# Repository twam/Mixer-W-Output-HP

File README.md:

Mixer-W-Output-HP
===

This repository is part of the USB audio mixer project described on https://www.twam.info/general/building-a-custom-usb-audio-mixer.

The 'W-Output HP' board is an W-Output compatible head phone amplifier, which can be used on
[W-DAC 4493](https://nihtila.com/2020/02/27/w-dac-4493-very-high-performance-compact-dac/) or
[W-DAC S 4493](https://nihtila.com/2020/12/28/w-dac-s-4493/). It is based on the
[HP Buf](https://nihtila.com/2018/02/04/hp-buf-high-current-buffered-amplifier-board-for-hp-mobo/) by
[Tomi Nihtilä](https://nihtila.com).

### Revision 1

Revision 1 misses two feedback resistors (R35, R36 in latest schematic):

Those can be easily bodged in with two through hole resistors:

### JLCPCB

PCBs can be ordered almost fully-assembled from [JLCPCB](https://jlcpcb.com/DDE). Required files are
[W-Output HP_cpl_jlc.csv](Gerber/W-Output%20HP_cpl_jlc.csv), [W-Output HP_bom_jlc.csv](Gerber/W-Output%20HP_bom_jlc.csv) and
[W-Output HP.zip](Gerber/W-Output%20HP.zip). Components missing are
* Two LME49600 on the buttom side of the board (U4, U5)
* Two 100uF electrolytic capacitors (C8, C21)
* Two NC3MBH-1 connectors (J4, J5)
* Two pin headers/pin sockets.

## License

[![CC BY-SA 4.0][cc-by-sa-shield]][cc-by-sa]

This work is licensed under a [Creative Commons Attribution-NonCommercial-ShareAlike 4.0 International License][cc-by-sa].

[![CC BY-SA 4.0][cc-by-sa-image]][cc-by-sa]

[cc-by-sa]: http://creativecommons.org/licenses/by-nc-sa/4.0/
[cc-by-sa-image]: https://licensebuttons.net/l/by-nc-sa/4.0/88x31.png
[cc-by-sa-shield]: https://img.shields.io/badge/License-CC%20BY--NC--SA%204.0-lightgrey.svg

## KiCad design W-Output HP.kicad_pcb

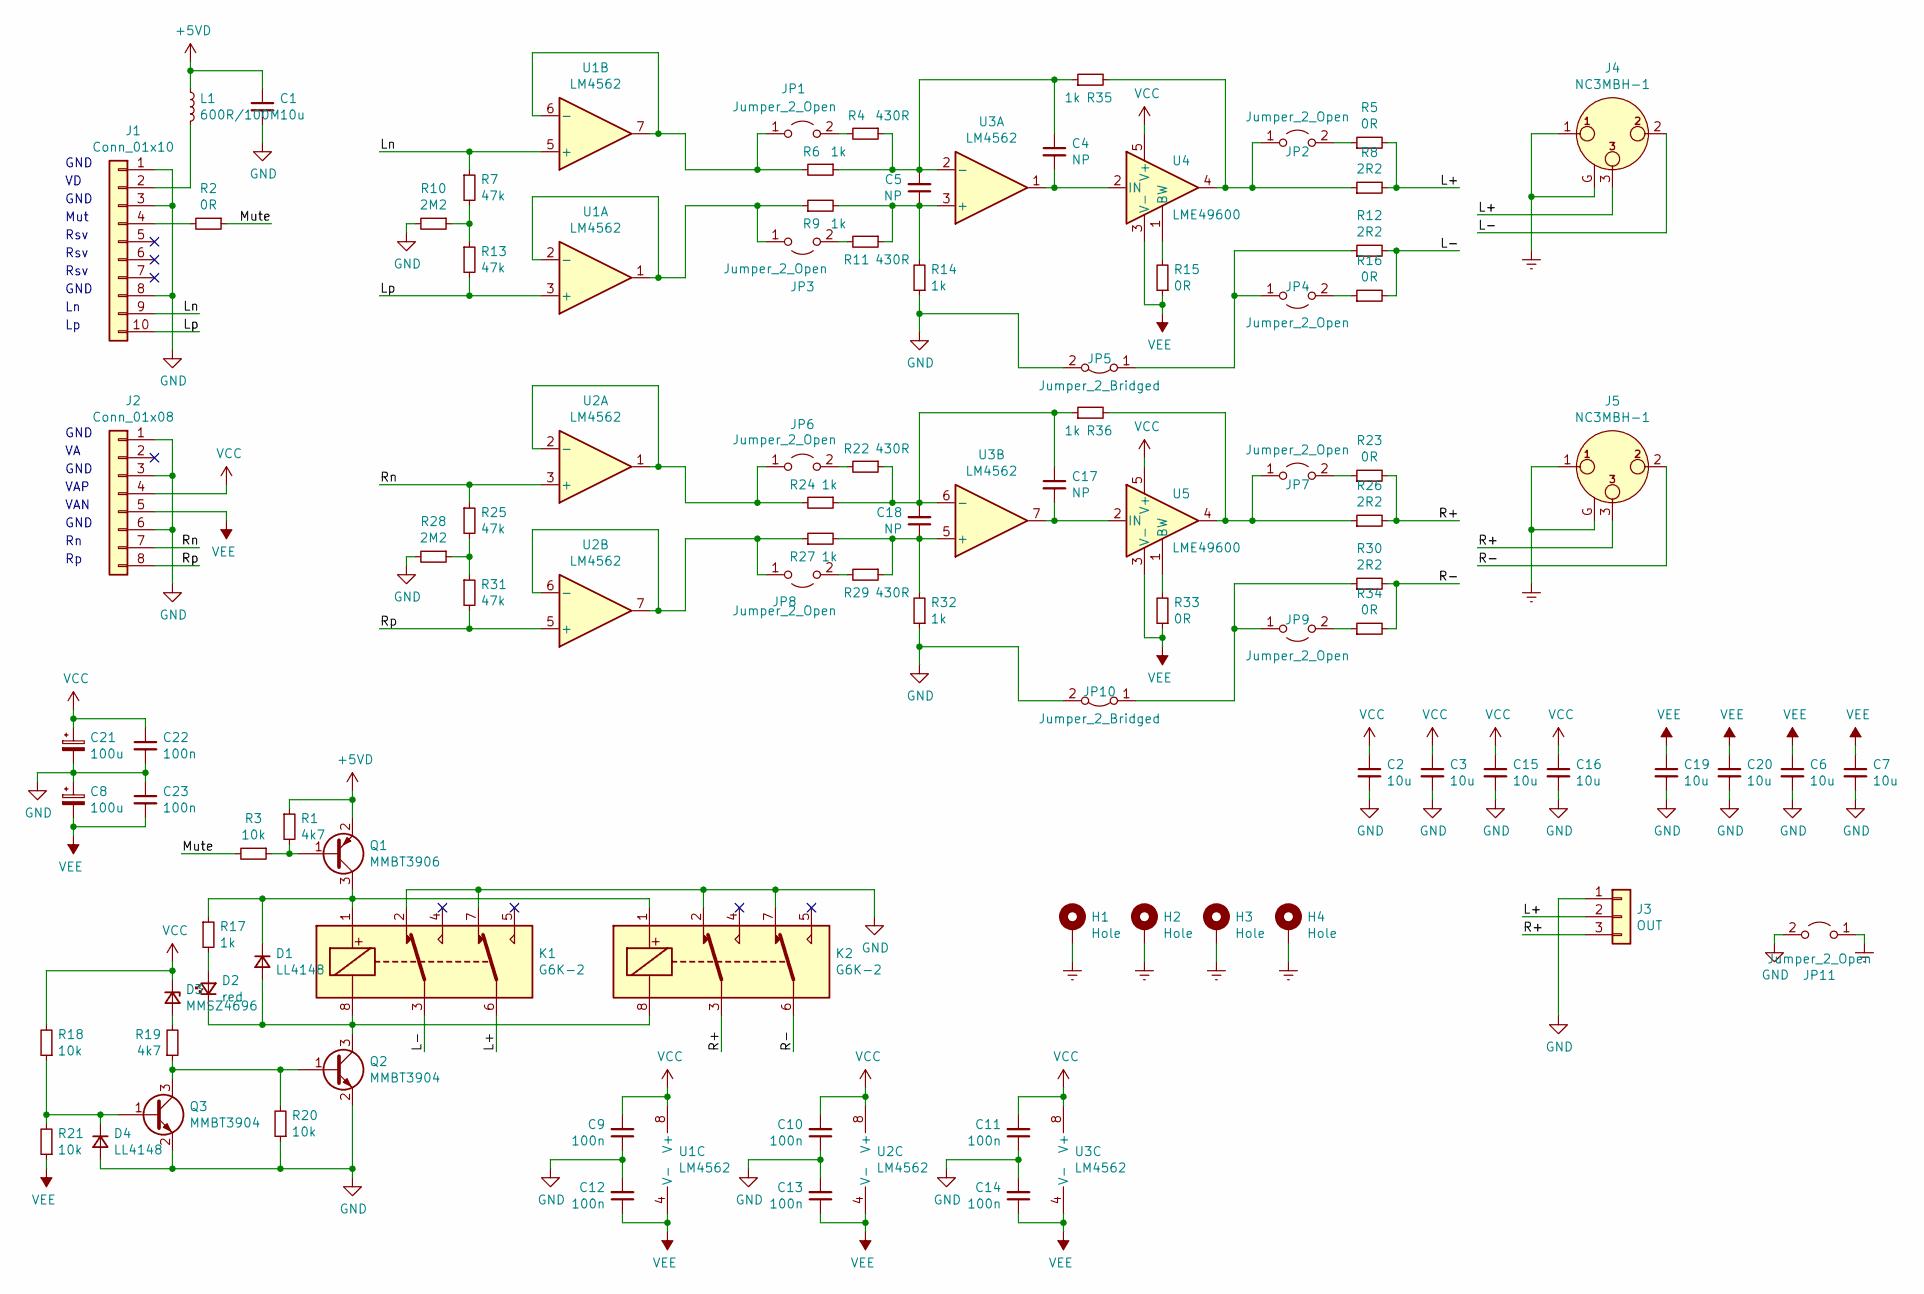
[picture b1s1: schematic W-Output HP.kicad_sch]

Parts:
C1, C2, C3, C6, C7, C15, C16, C19, C20: 10u; C_0805_2012Metric; LCSC C15850
C4, C5, C17, C18: NP; C_0603_1608Metric
C8, C21: 100u; CP_Radial_D6.3mm_P2.50mm
C9, C10, C11, C12, C13, C14, C22, C23: 100n; C_0603_1608Metric; LCSC C14663
D1, D4: LL4148; D_MiniMELF; LCSC C9808
D2: red; LED_0603_1608Metric; LCSC C2286
D3: MMSZ4696; D_SOD-123; LCSC C93559
H1, H2, H3, H4: Hole; MountingHole_3.2mm_M3_DIN965_Pad
J1: Conn_01x10; PinSocket_1x10_P2.54mm_Vertical
J2: Conn_01x08; PinSocket_1x08_P2.54mm_Vertical
J3: OUT; PinHeader_1x03_P2.54mm_Vertical
J4, J5: NC3MBH-1; Jack_XLR_Neutrik_NC3MBH_Horizontal
JP1, JP2, JP3, JP4, JP6, JP7, JP8, JP9, JP11: Jumper_2_Open; SolderJumper-2_P1.3mm_Open_RoundedPad1.0x1.5mm
JP5, JP10: Jumper_2_Bridged; SolderJumper-2_P1.3mm_Open_RoundedPad1.0x1.5mm
K1, K2: G6K-2; Relay_DPDT_Omron_G6K-2F-Y; LCSC C47190
L1: 600R/100M; L_0805_2012Metric; LCSC C1017
Q1: MMBT3906; SOT-23; LCSC C53444
Q2, Q3: MMBT3904; SOT-23; LCSC C81464
R1, R19: 4k7; R_0603_1608Metric; LCSC C23162
R2, R5, R15, R16, R23, R33, R34: 0R; R_0603_1608Metric; LCSC C21189
R3, R18, R20, R21: 10k; R_0603_1608Metric; LCSC C25804
R4, R11, R22, R29: 430R; R_0603_1608Metric; LCSC C23170
R6, R9, R14, R17, R24, R27, R32, R35, R36: 1k; R_0603_1608Metric; LCSC C21190
R7, R13, R25, R31: 47k; R_0603_1608Metric; LCSC C25819
R8, R12, R26, R30: 2R2; R_0603_1608Metric; LCSC C22939
R10, R28: 2M2; R_0603_1608Metric; LCSC C22938
U1, U2, U3: LM4562; SOIC-8_3.9x4.9mm_P1.27mm; LCSC C57367
U4, U5: LME49600; TO-263-5_TabPin3

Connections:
+5VD: C1.1, L1.1, Q1.2 (E), R1.1
/L+: J3.2, J4.3, K1.6, R5.2, R8.2
/L-: J4.2, K1.3, R12.2, R16.2
/Ln: J1.9, R7.1, U1.5 (+)
/Lp: J1.10, R13.2, U1.3 (+)
/Mute: R2.1, R3.2
/R+: J3.3, J5.3, K2.3, R23.2, R26.2
/R-: J5.2, K2.6, R30.2, R34.2
/Rn: J2.7, R25.1, U2.3 (+)
/Rp: J2.8, R31.2, U2.5 (+)
Earth: H1.1, H2.1, H3.1, H4.1, J4.1, J4.G, J5.1, J5.G, JP11.1 (A)
GND: C1.2, C2.2, C3.2, C6.2, C7.2, C8.1, C9.1, C10.1, C11.1, C12.2, C13.2, C14.2, C15.2, C16.2, C19.2, C20.2, C21.2, C22.2, C23.1, D4.2 (A), J1.1, J1.3, J1.8, J2.1, J2.3, J2.6, J3.1, JP5.2 (B), JP10.2 (B), JP11.2 (B), K1.2, K1.7, K2.2, K2.7, Q2.2 (E), Q3.2 (E), R10.2, R14.1, R20.1, R28.2, R32.1
unnamed: C4.1, C5.2, R4.1, R6.1, R35.1, U3.2 (-)
unnamed: C4.2, U3.1, U4.2 (IN)
unnamed: C5.1, R9.2, R11.1, R14.2, U3.3 (+)
unnamed: C17.1, C18.2, R22.1, R24.1, R36.1, U3.6 (-)
unnamed: C17.2, U3.7, U5.2 (IN)
unnamed: C18.1, R27.2, R29.1, R32.2, U3.5 (+)
unnamed: D1.1 (K), K1.1, K2.1, Q1.3 (C), R17.1
unnamed: D1.2 (A), D2.1 (K), K1.8, K2.8, Q2.3 (C)
unnamed: D2.2 (A), R17.2
unnamed: D3.2 (A), R19.2
unnamed: D4.1 (K), Q3.1 (B), R18.1, R21.2
unnamed: J1.2, L1.2
unnamed: J1.4, R2.2
unnamed: JP1.1 (A), R6.2, U1.6 (-), U1.7
unnamed: JP1.2 (B), R4.2
unnamed: JP2.1 (A), R8.1, R35.2, U4.4
unnamed: JP2.2 (B), R5.1
unnamed: JP3.1 (A), R9.1, U1.1, U1.2 (-)
unnamed: JP3.2 (B), R11.2
unnamed: JP4.1 (A), JP5.1 (A), R12.1
unnamed: JP4.2 (B), R16.1
unnamed: JP6.1 (A), R24.2, U2.1, U2.2 (-)
unnamed: JP6.2 (B), R22.2
unnamed: JP7.1 (A), R26.1, R36.2, U5.4
unnamed: JP7.2 (B), R23.1
unnamed: JP8.1 (A), R27.1, U2.6 (-), U2.7
unnamed: JP8.2 (B), R29.2
unnamed: JP9.2 (B), R34.1
unnamed: JP9.1 (A), JP10.1 (A), R30.1
unnamed: Q1.1 (B), R1.2, R3.1
unnamed: Q2.1 (B), Q3.3 (C), R19.1, R20.2
unnamed: R7.2, R10.1, R13.1
unnamed: R15.2, U4.1 (BW)
unnamed: R25.2, R28.1, R31.1
unnamed: R33.2, U5.1 (BW)
VCC: C2.1, C3.1, C9.2, C10.2, C11.2, C15.1, C16.1, C21.1, C22.1, D3.1 (K), J2.4, R18.2, U1.8 (V+), U2.8 (V+), U3.8 (V+), U4.5 (V+), U5.5 (V+)
VEE: C6.1, C7.1, C8.2, C12.1, C13.1, C14.1, C19.1, C20.1, C23.2, J2.5, R15.1, R21.1, R33.1, U1.4 (V-), U2.4 (V-), U3.4 (V-), U4.3 (V-), U5.3 (V-)

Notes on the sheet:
Mut
GND
Rsv
VAN
VAP

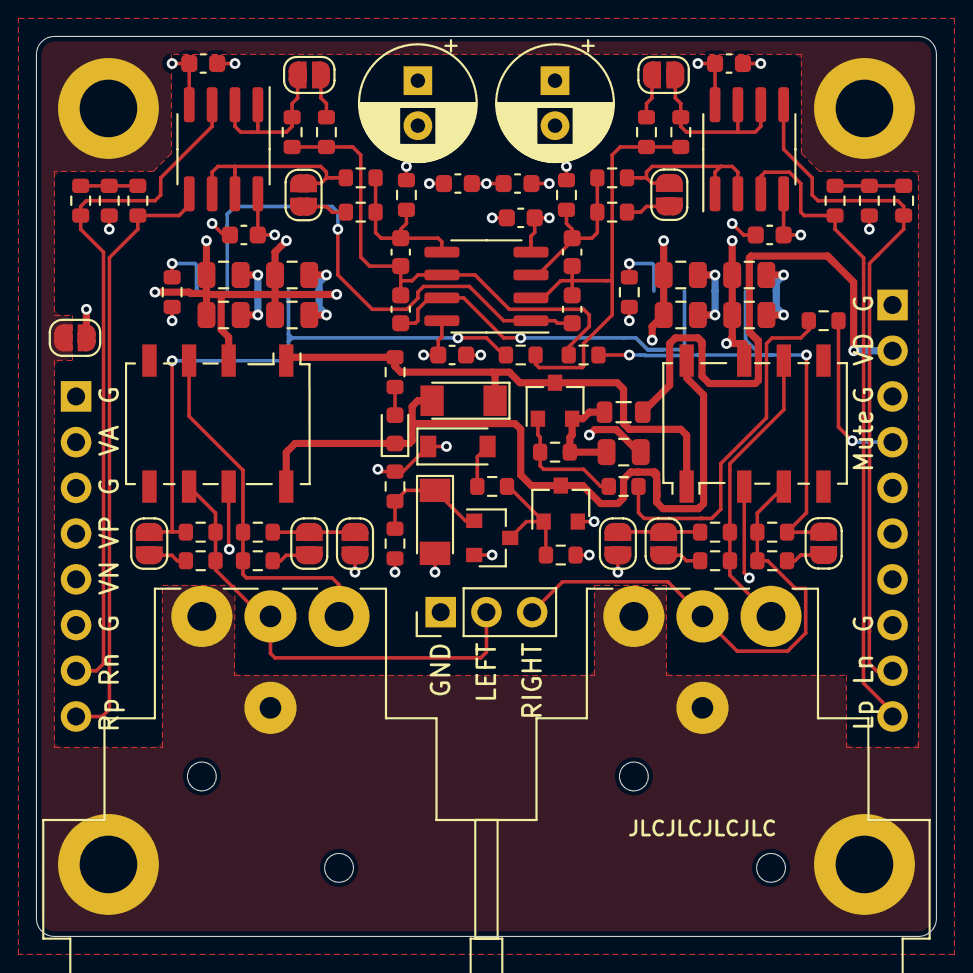
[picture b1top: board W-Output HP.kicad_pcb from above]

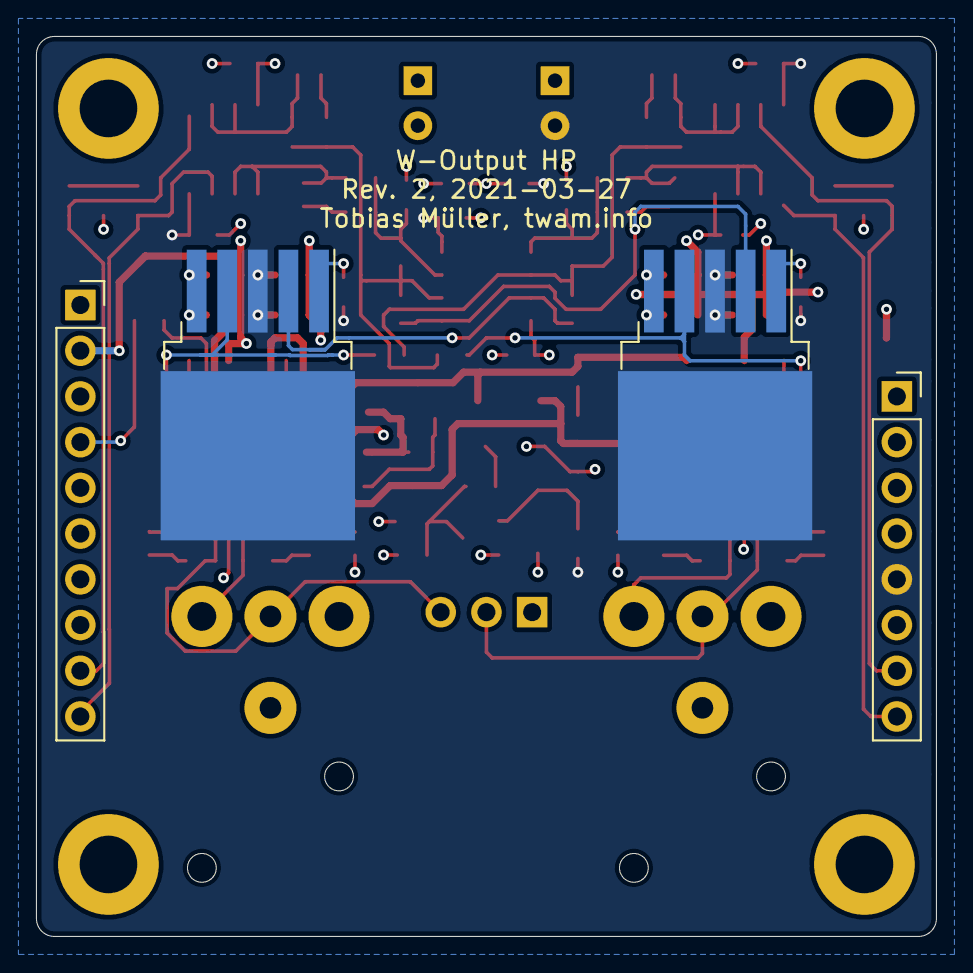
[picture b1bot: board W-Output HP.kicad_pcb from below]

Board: 4 copper layers, 50.0 x 50.0 mm, 94 parts (4 on the bottom side), 49 nets.

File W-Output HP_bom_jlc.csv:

"Comment","Designator","Footprint","LCSC Part #"
"10u","C1,C7,C6,C3,C2,C20,C19,C16,C15","C_0805_2012Metric","C15850"
"100n","C9,C12,C10,C13,C11,C14,C22,C23","C_0603_1608Metric","C14663"
"LL4148","D1,D4","D_MiniMELF","C9808"
"red","D2","LED_0603_1608Metric","C2286"
"MMSZ4696","D3","D_SOD-123","C93559"
"G6K-2","K1,K2","Relay_DPDT_Omron_G6K-2F-Y","C47190"
"600R/100M","L1","L_0805_2012Metric","C1017"
"MMBT3906","Q1","SOT-23","C53444"
"MMBT3904","Q2,Q3","SOT-23","C81464"
"4k7","R1,R19","R_0603_1608Metric","C23162"
"0R","R2,R15,R5,R16,R33,R23,R34","R_0603_1608Metric","C21189"
"10k","R3,R20,R18,R21","R_0603_1608Metric","C25804"
"430R","R4,R11,R22,R29","R_0603_1608Metric","C23170"
"47k","R7,R13,R25,R31","R_0603_1608Metric","C25819"
"2R2","R8,R26,R30,R12","R_0603_1608Metric","C22939"
"2M2","R10,R28","R_0603_1608Metric","C22938"
"1k","R17,R6,R9,R14,R24,R27,R32","R_0603_1608Metric","C21190"
"LM4562","U1,U2,U3","SOIC-8_3.9x4.9mm_P1.27mm","C57367"

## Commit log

2021-03-27 Initial commit. Rev 1.
2022-01-07 Add missing feedback resistor
2022-01-07 Update to KiCad 6
2022-01-07 Move JLCPCB files to Gerber
2022-01-07 Add Schematic Rev. 1
2022-01-09 Add README
